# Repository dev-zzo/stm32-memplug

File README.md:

# stm32-memplug

The `stm32-memplug` project aims to be a universal toy for playing with
various memory ICs. As is obvious from the name, it is based on the STM32
SoC series, more specifically the ever-popular STM32F103 chips.

The firmware bit sits on top of the code kindly provided by the
manufacturer, the "STM32CubeF1 MCU Firmware Package". At least some part
of it will have to be rewritten later to support the flexibility I want it
to have.

The hardware bit mostly relies on the FSMC unit to handle all the signalling
for NOR, NAND, and eMMC chips.

**CAUTION**: The hardware supports 3v3 chips only. 1v8 chips **will** be destroyed.

# Why would you even?

> Science is not about *why*! It's about *why not*?

This toy is meant for learning and experimenting, not for any kind of
"professional work". Hack it and have fun while learning about the F103
and different memory types.

# How to do anything useful with this?

The toy relies on PA3..0 to detect which memory type it should configure:

PA3..0 | Memory type
-------|------------
0000 | eMMC
0001 | NAND
0011 | NOR
Other | Reserved

If you forget to set those pins to known values, the board will show up as
`STM32-MemPlug: Unknown TOP` in your USB devices.

## eMMC devices

Connect your eMMC chip to the STM32F103 board:

eMMC pin | F103 pin
---------|---------
CLK | PC12
CMD | PD2
D0 | PC8
D1 | PC9
D2 | PC10
D3 | PC11
nRST | PA8

eMMC D4 through D7 are not used anyway at this point (see Performance).
Remember to connect 3.3V and GND too! Note that some eMMC chips will require
connecting most or all power pads.

Both standard and high capacity devices should be supported.

If everything works fine, the device will appear as a simple USB mass storage
when connected to the host system. When the chip is accessed, the PC13 LED
will light up for visual confirmation.

### Wishlist

* Accessing boot partitions

## NOR devices

The current firmware supports x16 parallel-NOR chips. Wire them up like this:

NOR pin | F103 pin
--------|---------
 A0 | PF0
 A1 | PF1
 A2 | PF2
 A3 | PF3
 A4 | PF4
 A5 | PF5
 A6 | PF12
 A7 | PF13
 A8 | PF14
 A9 | PF15
A10 | PG0
A11 | PG1
A12 | PG2
A13 | PG3
A14 | PG4
A15 | PG5
A16 | PD11
A17 | PD12
A18 | PD13
A19 | PE3
A20 | PE4
A21 | PE5
A22 | PE6
A23 | PE2
A24 | PG13
A15 | PG14
 D0 | PD14
 D1 | PD15
 D2 | PD0
 D3 | PD1
 D4 | PE7
 D5 | PE8
 D6 | PE9
 D7 | PE10
 D8 | PE11
 D9 | PE12
D10 | PE13
D11 | PE14
D12 | PE15
D13 | PD8
D14 | PD9
D15 | PD10
nCE | PD7
nOE | PD4
nWE | PD5
R/B | PD6

Note the `R/B` signal might need a 10k pull-up; the internal pull-up might be
too weak to be fast enough.

## NAND devices

That is yet to come. :-)

# Building firmware

A Makefile is provided which should do that for you. Just run `make` from the
root dir. The script relies on the `CROSS_COMPILE` environment variable to
find the right compiler; it should be set to the path and prefix of your ARM
compiler; for example, it's `~/x-tools/arm-none-eabi/bin/arm-none-eabi-` on my system.

# Building hardware

If you don't want to wire small things all the time, several board designs have been
created as a semi-permanent solution. You can find those designs under `hardware`.

The general approach is, one "top" board is provided for each memory type, this goes
directly on top of the STM32F103ZE "minimal system board" (the cheapest option).
The top board provides wiring and passives as needed and accepts a set of small
footprint-specific boards; you can solder your target to those boards for reliable
and fast connection.

This is especially useful for BGA chips:

* Removing them from the device-under-hack requires hot air / rework station anyway
* Reballing the chip needs to be done anyway, doing it twice doesn't take as long

# Performance

The design is limited mostly by the USB unit of the F103 at the moment.
The theoretical speed is no greater than 1MB/s, so don't expect blazing
rates here. Transfer speeds are about 250KB/s writing and 450KB/s reading.

NOR Flash read speeds tend to land somewhere around 700KB/s.

# Debugging

The toy uses Serial Wire Output (SWO) to pring debugging messages in cases when
things go sideways; having a dongle which is able to receive that is advised.

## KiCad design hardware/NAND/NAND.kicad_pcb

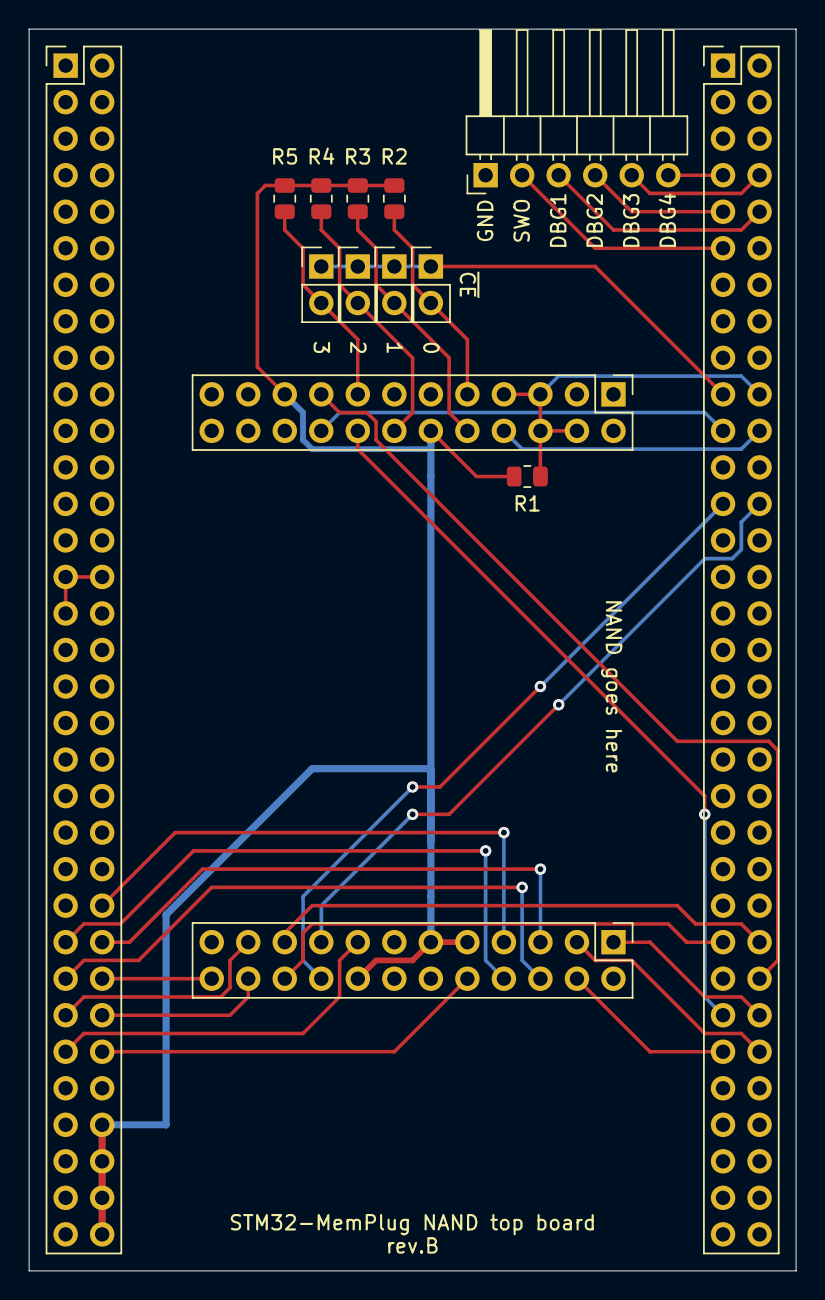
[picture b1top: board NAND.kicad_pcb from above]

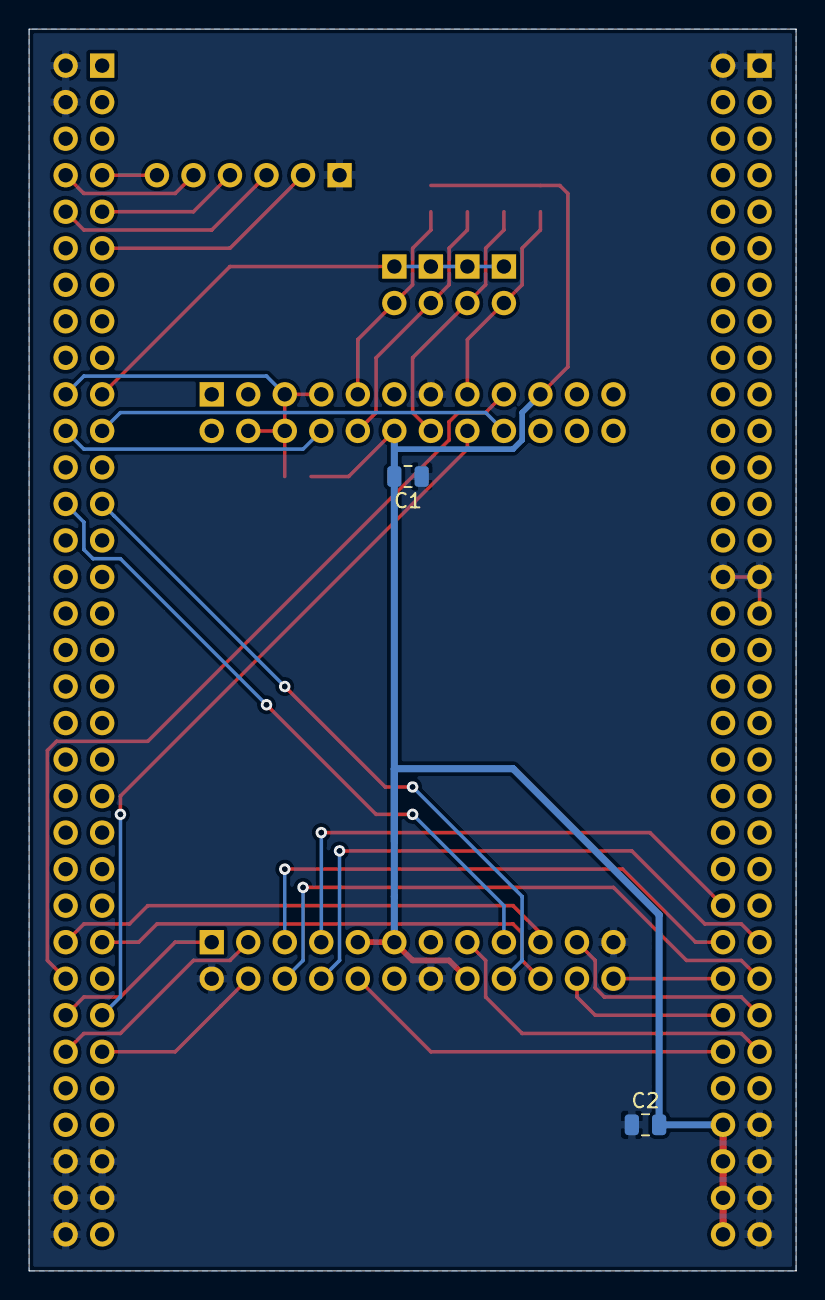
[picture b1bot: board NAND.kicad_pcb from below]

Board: 2 copper layers, 53.3 x 86.4 mm, 16 parts (2 on the bottom side), 33 nets.

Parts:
C1, C2: 100n; C_0805_2012Metric
J1: Left; PinHeader_2x33_P2.54mm_Vertical
J2: Right; PinHeader_2x33_P2.54mm_Vertical
J3: DBG; PinHeader_1x06_P2.54mm_Horizontal
J4: Left; PinHeader_2x12_P2.54mm_Vertical
J5: Right; PinHeader_2x12_P2.54mm_Vertical
JP1: CE0; PinHeader_1x02_P2.54mm_Vertical
JP2: CE1; PinHeader_1x02_P2.54mm_Vertical
JP3: CE2; PinHeader_1x02_P2.54mm_Vertical
JP4: CE3; PinHeader_1x02_P2.54mm_Vertical
R1: 1k; R_0805_2012Metric
R2, R3, R4, R5: 10k; R_0805_2012Metric

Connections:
+3V3: C1.2, C2.2, J1.60, J1.62, J1.64, J1.66, J4.12, J4.19, J5.9, J5.11, J5.16, R1.1, R2.1, R3.1, R4.1, R5.1
ALE: J2.52, J4.17
CLE: J2.53, J4.16
GND: C1.1, C2.1, J1.1, J1.2, J1.29, J1.30, J1.59, J1.61, J1.63, J1.65, J2.2, J2.4, J2.61, J2.62, J2.63, J2.64, J2.66, J3.1, J4.13, J5.2, J5.14, J5.23
IO0: J2.50, J5.19
IO1: J2.49, J5.20
IO2: J2.26, J5.17
IO3: J2.25, J5.18
IO4: J1.48, J5.7
IO5: J1.49, J5.8
IO6: J1.50, J5.5
IO7: J1.51, J5.6
IO8: J1.52, J5.24
IO9: J1.53, J5.21
IO10: J1.54, J5.22
IO11: J1.55, J5.15
IO12: J1.56, J5.10
IO13: J2.56, J5.3
IO14: J2.55, J5.4
IO15: J2.54, J5.1
PB3: J2.11, J3.2
PB4: J2.10, J3.3
PB5: J2.9, J3.4
PB6: J2.8, J3.5
PB7: J2.7, J3.6
R~B: J2.20, J4.4, J4.5, J4.6, J4.7, R1.2
~CE: J2.19, JP1.1, JP2.1, JP3.1, JP4.1
~CE0: J4.9, JP1.2, R2.2
~CE1: J4.10, JP2.2, R3.2
~CE2: J4.14, JP3.2, R4.2
~CE3: J4.15, JP4.2, R5.2
~RE: J2.22, J4.8
~WE: J2.21, J4.18

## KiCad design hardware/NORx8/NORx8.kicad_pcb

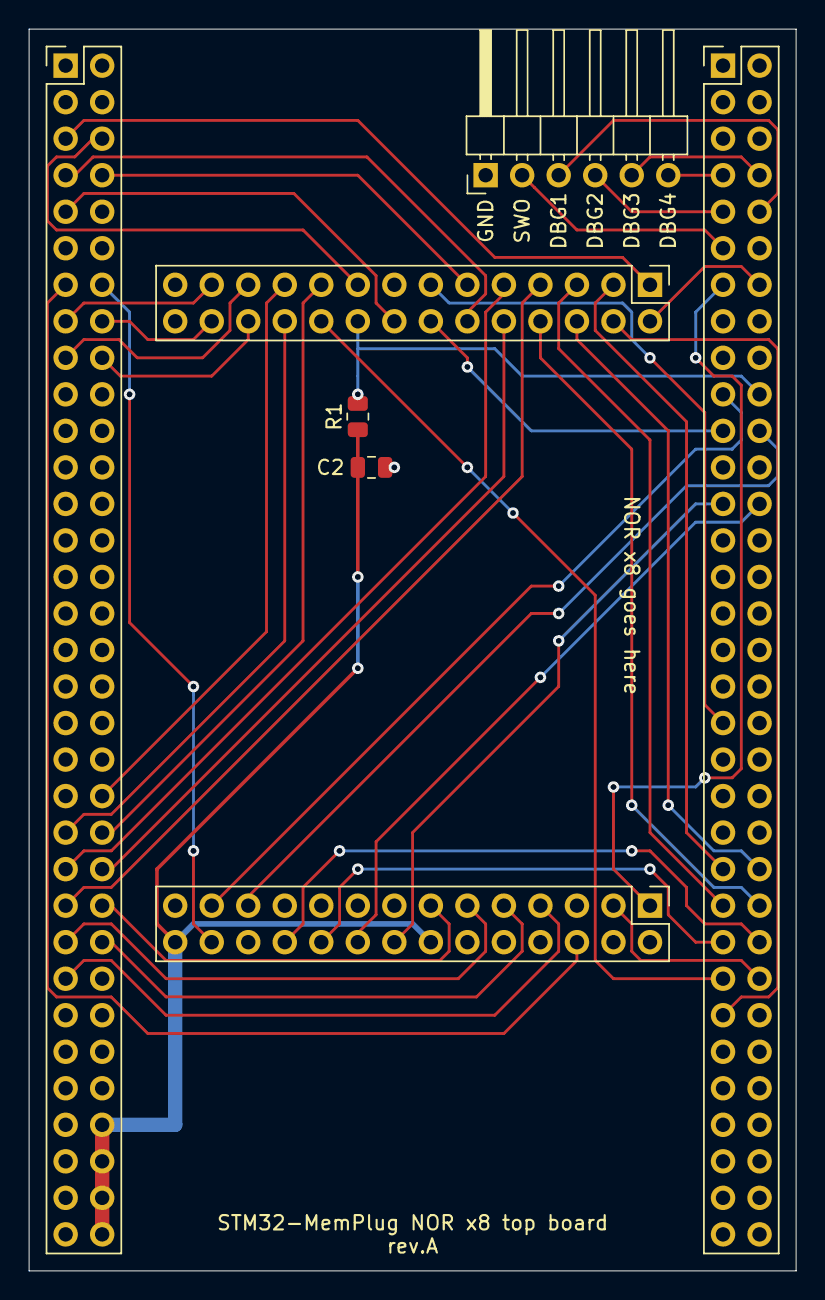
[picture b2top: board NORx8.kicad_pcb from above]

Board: 2 copper layers, 53.3 x 86.4 mm, 8 parts (1 on the bottom side), 46 nets.

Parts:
C1, C2: 100n; C_0805_2012Metric
J1: Left; PinHeader_2x33_P2.54mm_Vertical
J2: Right; PinHeader_2x33_P2.54mm_Vertical
J3: DBG; PinHeader_1x06_P2.54mm_Horizontal
J4: Left; PinHeader_2x14_P2.54mm_Vertical
J5: Right; PinHeader_2x14_P2.54mm_Vertical
R1: 10k; R_0805_2012Metric

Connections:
+3V3: C1.2, C2.2, J1.60, J1.62, J1.64, J1.66, J5.14, J5.28, R1.1
A0: J1.13, J5.6
A1: J1.14, J5.26
A2: J1.15, J4.25
A3: J1.16, J4.26
A4: J1.17, J4.23
A5: J1.18, J4.24
A6: J1.42, J4.21
A7: J1.43, J4.22
A8: J1.44, J4.19
A9: J1.45, J4.9
A10: J1.46, J4.10
A11: J1.47, J4.7
A12: J2.48, J4.8
A13: J2.47, J4.5
A14: J2.46, J4.6
A15: J2.45, J4.3
A16: J2.53, J4.4
A17: J2.52, J5.3
A18: J2.51, J4.20
A19: J1.6, J4.17
A20: J1.7, J4.12
A21: J1.8, J4.11
A22: J1.9, J4.16
A23: J1.5, J4.1
A24: J2.14, J4.2
A25: J2.13, J5.1
GND: C1.1, C2.1, J1.1, J1.2, J1.28, J1.30, J1.31, J1.59, J1.61, J1.63, J1.65, J2.2, J2.4, J2.61, J2.62, J2.63, J2.64, J2.66, J3.1, J5.5, J5.24
IO0: J2.50, J5.22
IO1: J2.49, J5.20
IO2: J2.26, J5.18
IO3: J2.25, J5.16
IO4: J1.48, J5.13
IO5: J1.49, J5.11
IO6: J1.50, J5.9
IO7: J1.51, J5.7
PB3: J2.11, J3.2
PB4: J2.10, J3.3
PB5: J2.9, J3.4
PB6: J2.8, J3.5
PB7: J2.7, J3.6
R~B: J2.20, J4.18, R1.2
~CE: J2.19, J5.25
~OE: J2.22, J5.23
~RST: J2.37, J4.13
~WE: J2.21, J4.14

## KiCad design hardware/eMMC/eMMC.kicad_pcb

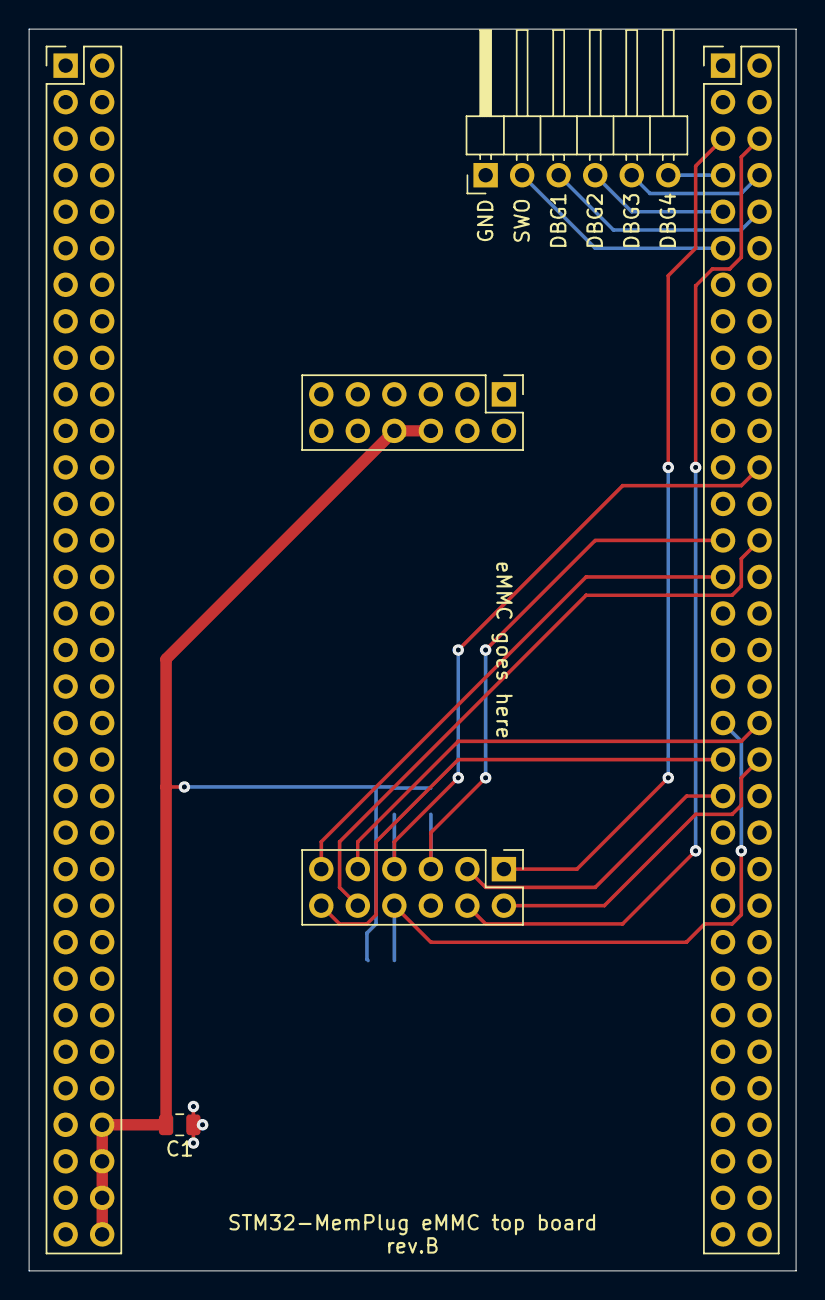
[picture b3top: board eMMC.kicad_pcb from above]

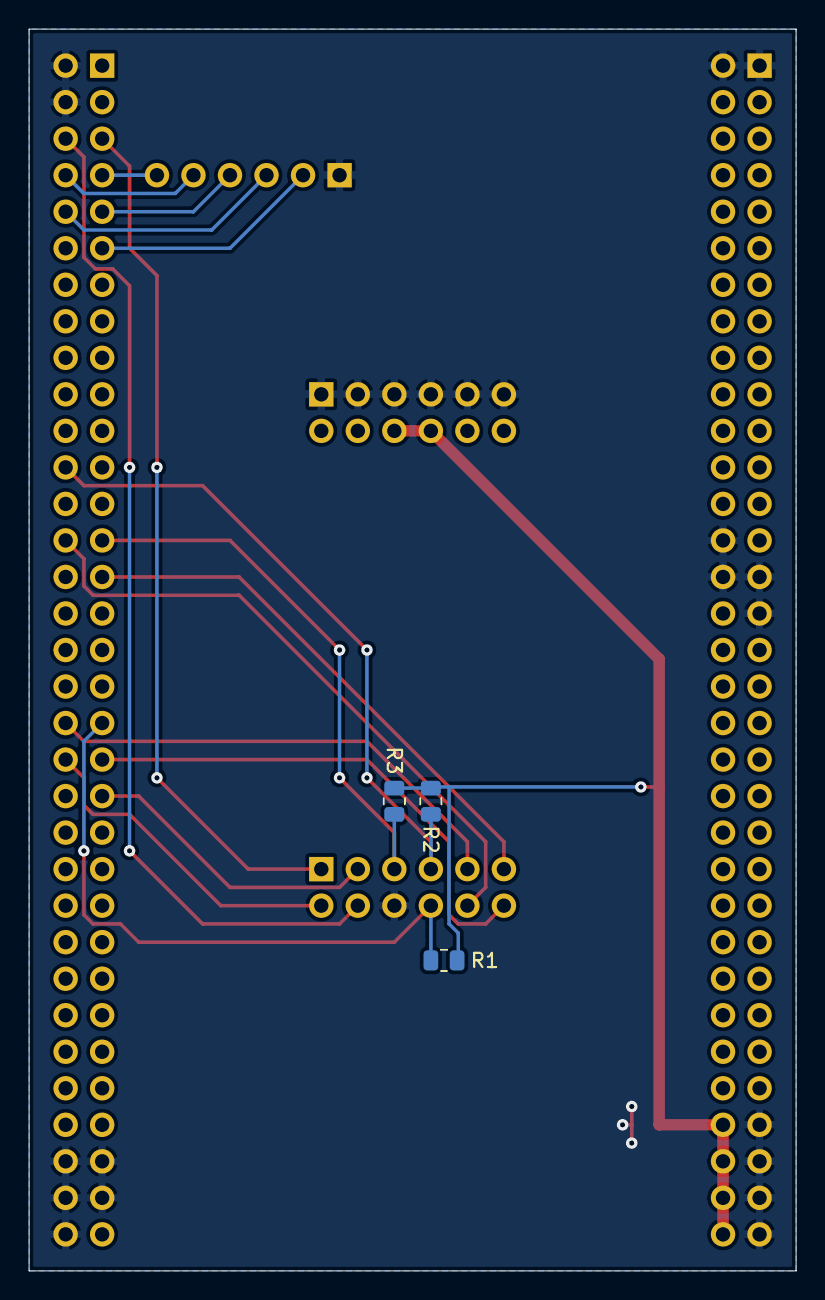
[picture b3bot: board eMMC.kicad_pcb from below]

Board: 2 copper layers, 53.3 x 86.4 mm, 9 parts (3 on the bottom side), 18 nets.

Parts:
C1: 100n; C_0805_2012Metric
J1: Left; PinHeader_2x33_P2.54mm_Vertical
J2: Right; PinHeader_2x33_P2.54mm_Vertical
J3: DBG; PinHeader_1x06_P2.54mm_Horizontal
J4: Left; PinHeader_2x06_P2.54mm_Vertical
J5: Right; PinHeader_2x06_P2.54mm_Vertical
R1, R2, R3: 10k; R_0805_2012Metric

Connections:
+3V3: C1.2, J1.60, J1.62, J1.64, J1.66, J4.6, J4.8, R1.1, R2.1, R3.1
CLK: J2.27, J5.5, R3.2
CMD: J2.24, J5.7, R2.2
DAT0: J2.39, J5.12
DAT1: J2.38, J5.9
DAT2: J2.29, J5.11
DAT3: J2.28, J5.10
DAT4: J2.6, J5.4
DAT5: J2.5, J5.1
DAT6: J2.41, J5.3
DAT7: J2.40, J5.2
GND: C1.1, J1.1, J1.2, J1.28, J1.29, J1.30, J1.31, J1.59, J1.61, J1.63, J1.65, J2.2, J2.4, J2.61, J2.62, J2.63, J2.64, J2.66, J3.1, J4.1, J4.3, J4.5, J4.7, J4.9, J4.11, J5.6
PB3: J2.11, J3.2
PB4: J2.10, J3.3
PB5: J2.9, J3.4
PB6: J2.8, J3.5
PB7: J2.7, J3.6
~RST: J2.37, J5.8, R1.2

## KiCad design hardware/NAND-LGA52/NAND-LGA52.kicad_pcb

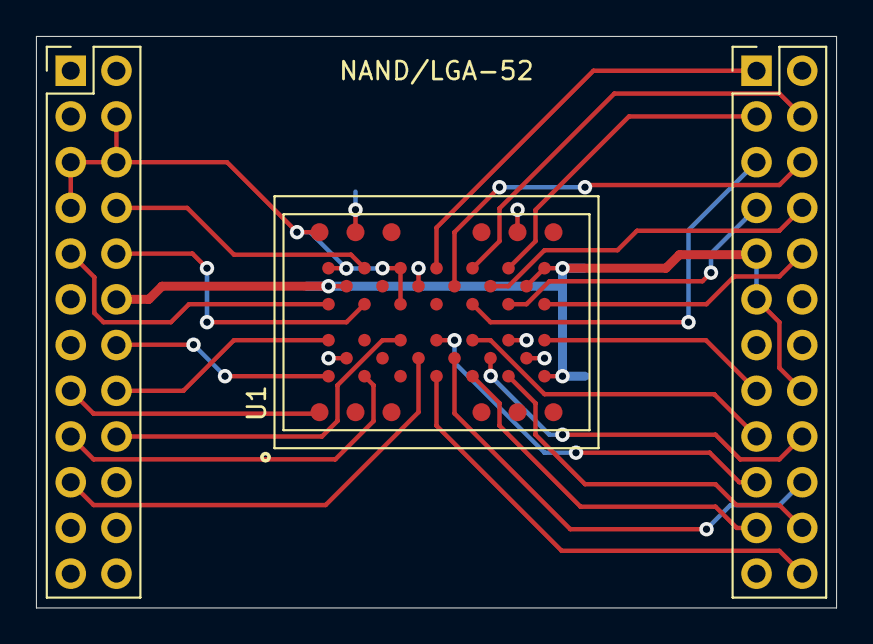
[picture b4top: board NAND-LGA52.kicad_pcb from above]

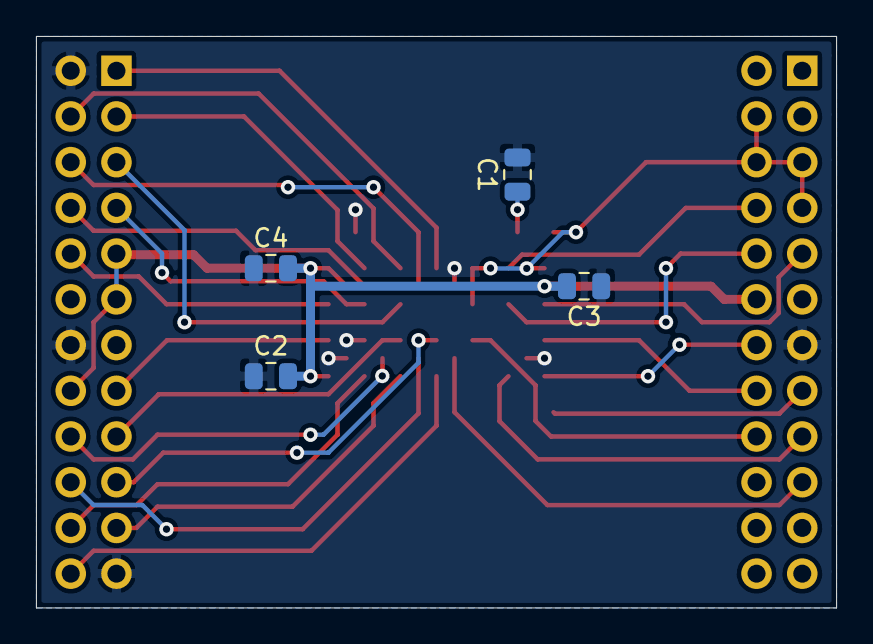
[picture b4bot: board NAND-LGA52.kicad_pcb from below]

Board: 2 copper layers, 44.4 x 31.8 mm, 7 parts (4 on the bottom side), 29 nets.

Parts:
C1, C2, C3, C4: 100n; C_0805_2012Metric
J1: Left; PinHeader_2x12_P2.54mm_Vertical
J2: Right; PinHeader_2x12_P2.54mm_Vertical
U1: Generic_ONFI_NAND_LGA52; LGA52C100P7X13_UNI

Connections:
+3V3: C2.2, C3.2, C4.2, J1.12, J2.9, J2.11, J2.16, U1.B6, U1.M6, U1.N1, U1.N7
ALE: J1.17, U1.C1
CLE: J1.16, U1.A3
GND: C1.2, C2.1, C3.1, C4.1, J1.13, J2.2, J2.14, J2.23, U1.B2, U1.F6, U1.L3, U1.M2, U1.OE8
IO0: J2.19, U1.G3
IO1: J2.20, U1.H2
IO2: J2.17, U1.J3
IO3: J2.18, U1.K2
IO4: J2.7, U1.L5
IO5: J2.8, U1.K6
IO6: J2.5, U1.J5
IO7: J2.6, U1.H6
IO8: J2.24, U1.G1
IO9: J2.21, U1.J1
IO10: J2.22, U1.L1
IO11: J2.15, U1.N3
IO12: J2.10, U1.N5
IO13: J2.3, U1.L7
IO14: J2.4, U1.J7
IO15: J2.1, U1.G7
unnamed: C1.1, U1.OB8
R~B: J1.4, J1.5, J1.6, J1.7, U1.A7, U1.E5, U1.E7, U1.OA8
~CE0: J1.9, U1.A5
~CE1: J1.10, U1.C5
~CE2: J1.14, U1.A1
~CE3: J1.15, U1.OA0
~RE: J1.8, U1.C7
~WE: J1.18, U1.E3
~WP: J1.19, U1.F2

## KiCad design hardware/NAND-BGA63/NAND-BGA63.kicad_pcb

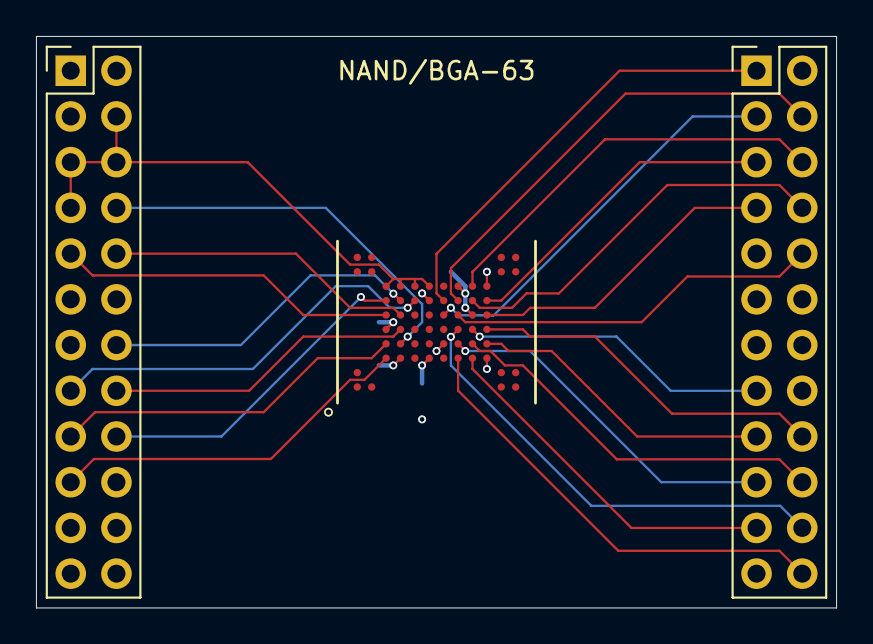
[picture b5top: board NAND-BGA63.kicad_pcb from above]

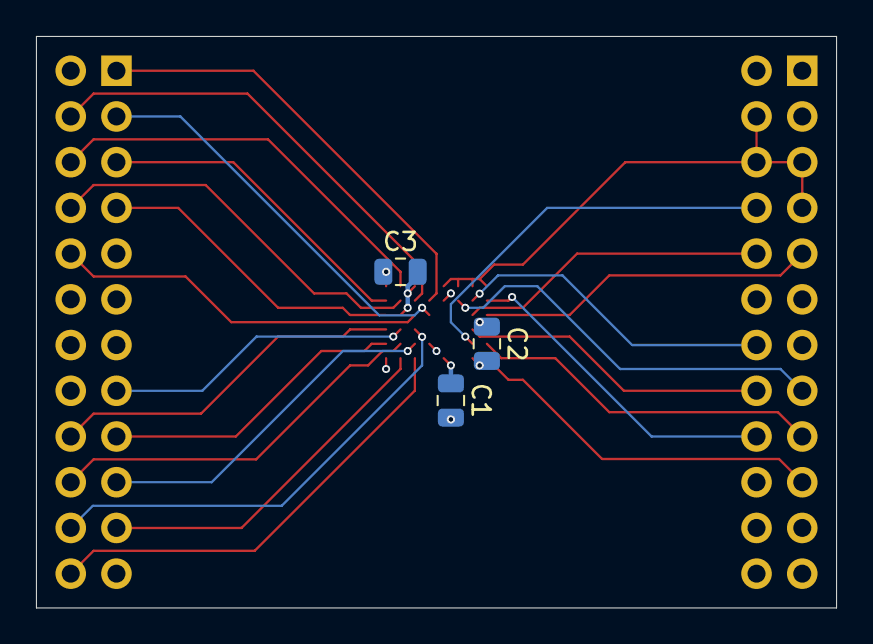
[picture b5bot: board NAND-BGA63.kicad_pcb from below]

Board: 4 copper layers, 44.5 x 31.8 mm, 6 parts (3 on the bottom side), 29 nets.

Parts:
C1, C2, C3: 100n; C_0805_2012Metric
J1: Left; PinHeader_2x12_P2.54mm_Vertical
J2: Right; PinHeader_2x12_P2.54mm_Vertical
U1: Generic_ONFI_NAND_BGA63; BGA63C80P12X10_1100X900X120

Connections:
+3V3: C2.2, C3.2, J1.12, J2.9, J2.11, J2.16, U1.D3, U1.G4, U1.H8, U1.J6
ALE: J1.17, U1.C4
CLE: J1.16, U1.D5
GND: C1.2, C2.1, C3.1, J1.13, J2.2, J2.14, J2.23, U1.C5, U1.F7, U1.K3, U1.K8
IO0: J2.19, U1.H4
IO1: J2.20, U1.J4
IO2: J2.17, U1.K4
IO3: J2.18, U1.K5
IO4: J2.7, U1.K6
IO5: J2.8, U1.J7
IO6: J2.5, U1.K7
IO7: J2.6, U1.J8
IO8: J2.24, U1.H3
IO9: J2.21, U1.J3
IO10: J2.22, U1.H5
IO11: J2.15, U1.J5
IO12: J2.10, U1.H6
IO13: J2.3, U1.G6
IO14: J2.4, U1.H7
IO15: J2.1, U1.G7
unnamed: C1.1, U1.F3
R~B: J1.4, J1.5, J1.6, J1.7, U1.C8, U1.D8, U1.E8, U1.F8
~CE0: J1.9, U1.C6
~CE1: J1.10, U1.D6
~CE2: J1.14, U1.D7
~CE3: J1.15, U1.E7
~RE: J1.8, U1.D4
~WE: J1.18, U1.C7
~WP: J1.19, U1.C3

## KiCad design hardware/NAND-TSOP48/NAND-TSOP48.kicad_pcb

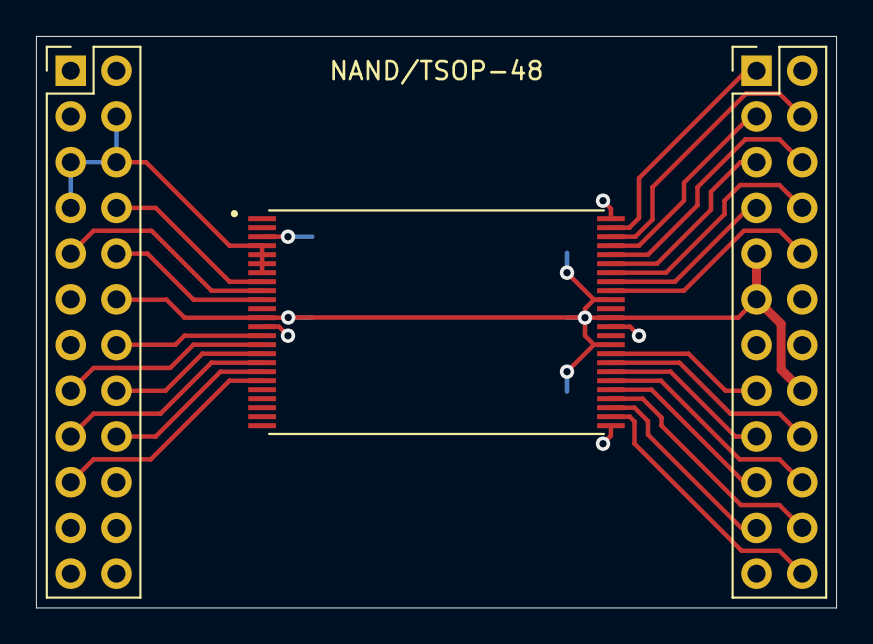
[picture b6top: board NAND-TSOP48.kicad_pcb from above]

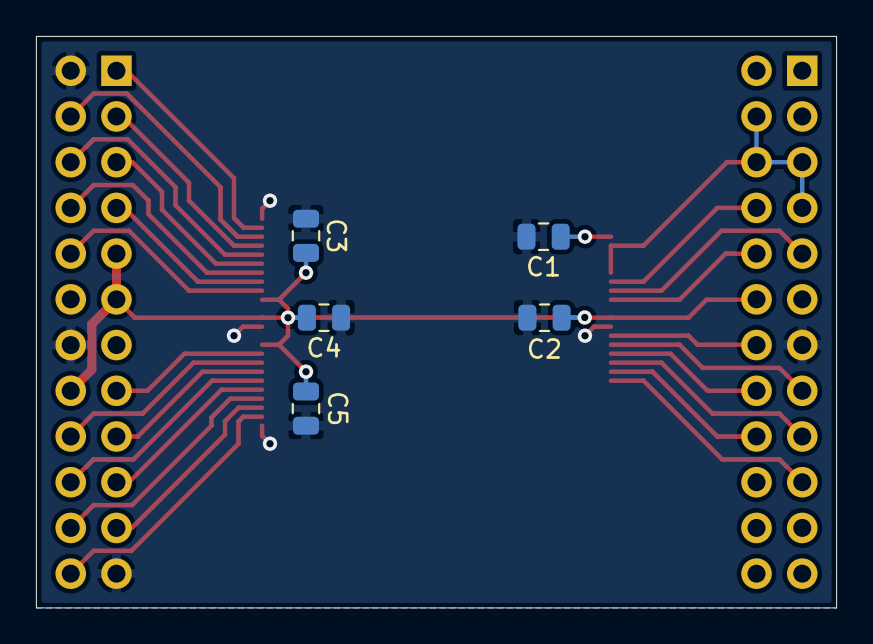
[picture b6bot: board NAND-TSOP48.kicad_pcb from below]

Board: 2 copper layers, 44.5 x 31.7 mm, 8 parts (5 on the bottom side), 29 nets.

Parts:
C1, C2, C3, C4, C5: 100n; C_0805_2012Metric
J1: Left; PinHeader_2x12_P2.54mm_Vertical
J2: Right; PinHeader_2x12_P2.54mm_Vertical
U1: Generic_ONFI_NAND_TSOP48; SOP50P2000X120-48N

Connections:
+3V3: C2.2, C3.2, C4.2, C5.2, J1.12, J2.9, J2.11, J2.16, U1.12, U1.34, U1.37, U1.39
ALE: J1.17, U1.17
CLE: J1.16, U1.16
GND: C1.2, C2.1, C3.1, C4.1, C5.1, J1.13, J2.2, J2.14, J2.23, U1.13, U1.25, U1.36, U1.48
IO0: J2.19, U1.29
IO1: J2.20, U1.30
IO2: J2.17, U1.31
IO3: J2.18, U1.32
IO4: J2.7, U1.41
IO5: J2.8, U1.42
IO6: J2.5, U1.43
IO7: J2.6, U1.44
IO8: J2.24, U1.26
IO9: J2.21, U1.27
IO10: J2.22, U1.28
IO11: J2.15, U1.33
IO12: J2.10, U1.40
IO13: J2.3, U1.45
IO14: J2.4, U1.46
IO15: J2.1, U1.47
unnamed: C1.1, U1.3
R~B: J1.4, J1.5, J1.6, J1.7, U1.4, U1.5, U1.6, U1.7
~CE0: J1.9, U1.9
~CE1: J1.10, U1.10
~CE2: J1.14, U1.14
~CE3: J1.15, U1.15
~RE: J1.8, U1.8
~WE: J1.18, U1.18
~WP: J1.19, U1.19

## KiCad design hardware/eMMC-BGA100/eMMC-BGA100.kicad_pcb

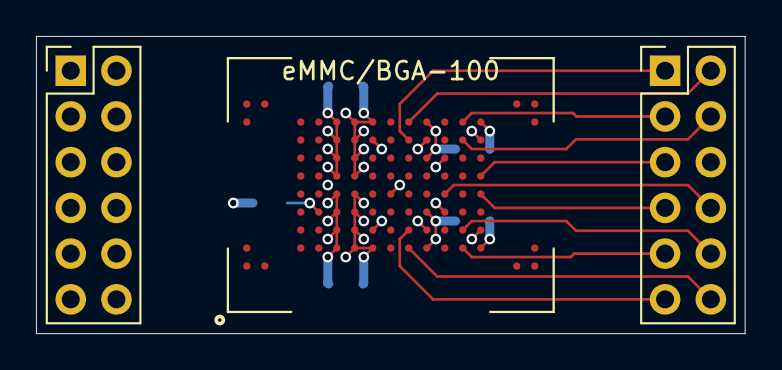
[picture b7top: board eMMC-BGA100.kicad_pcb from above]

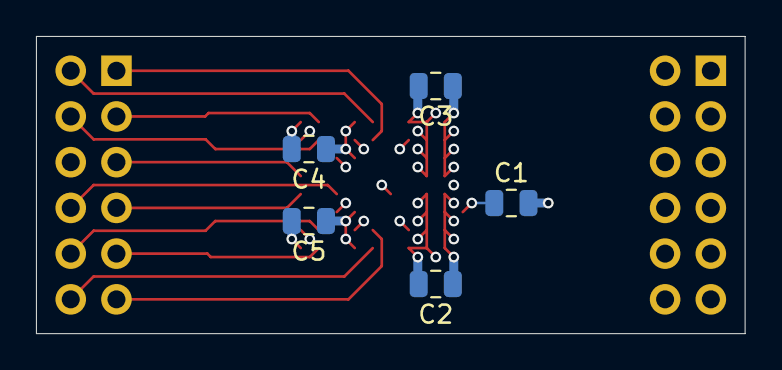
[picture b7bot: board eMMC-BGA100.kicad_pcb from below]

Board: 4 copper layers, 39.4 x 16.5 mm, 8 parts (5 on the bottom side), 14 nets.

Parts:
C1, C2, C3, C4, C5: 100n; C_0805_2012Metric
J1: Left; PinHeader_2x06_P2.54mm_Vertical
J2: Right; PinHeader_2x06_P2.54mm_Vertical
U1: Generic_eMMC_BGA100; BGA100C100P17X10_1800X1400X140N

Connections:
+3V3: C2.1, C3.1, C4.1, C5.1, J1.6, J1.8, U1.F2, U1.F3, U1.F4, U1.F5, U1.F6, U1.F7, U1.F8, U1.F9, U1.H3, U1.H8, U1.L2, U1.L4, U1.L7, U1.L9, U1.P3, U1.P8
CLK: J2.5, U1.P6
CMD: J2.7, U1.P5
DAT0: J2.12, U1.K2
DAT1: J2.9, U1.N2
DAT2: J2.11, U1.K3
DAT3: J2.10, U1.N3
DAT4: J2.4, U1.N8
DAT5: J2.1, U1.K8
DAT6: J2.3, U1.N9
DAT7: J2.2, U1.K9
GND: C1.2, C2.2, C3.2, C4.2, C5.2, J1.1, J1.3, J1.5, J1.7, J1.9, J1.11, J2.6, U1.G2, U1.G3, U1.G4, U1.G5, U1.G6, U1.G7, U1.G8, U1.G9, U1.H2, U1.H9, U1.J5, U1.L3, U1.L8, U1.M4, U1.M7, U1.P2, U1.P9
unnamed: C1.1, U1.E4
~RST: J2.8, U1.M5

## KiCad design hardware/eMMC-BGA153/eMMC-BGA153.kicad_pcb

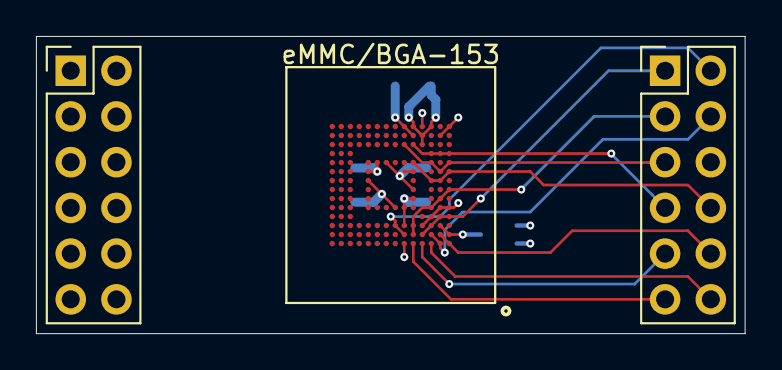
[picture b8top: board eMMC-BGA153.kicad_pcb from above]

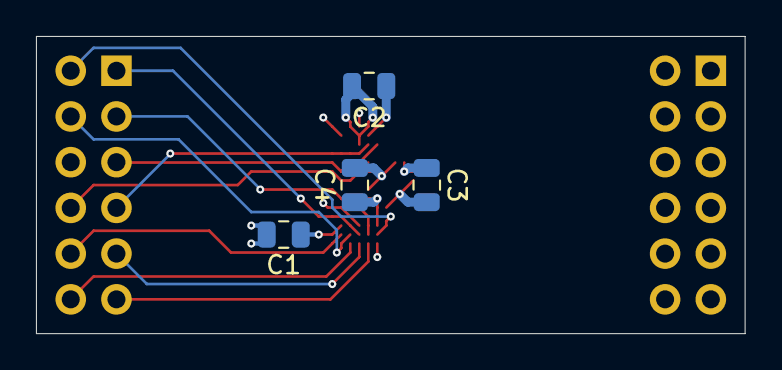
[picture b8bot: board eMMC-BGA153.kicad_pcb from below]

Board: 4 copper layers, 39.4 x 16.5 mm, 7 parts (4 on the bottom side), 14 nets.

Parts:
C1, C2, C3, C4: 100n; C_0805_2012Metric
J1: Left; PinHeader_2x06_P2.54mm_Vertical
J2: Right; PinHeader_2x06_P2.54mm_Vertical
U1: Generic_eMMC_BGA153; BGA153N50P14X14_1150X1300X100

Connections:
+3V3: C2.1, C3.1, C4.1, J1.6, J1.8, U1.C6, U1.E6, U1.F5, U1.J10, U1.K9, U1.M4, U1.N4, U1.P3, U1.P5
CLK: J2.5, U1.J2, U1.K1, U1.K3, U1.M6
CMD: J2.7, U1.L1, U1.L2, U1.L3, U1.M5
DAT0: J2.12, U1.A3
DAT1: J2.9, U1.A4
DAT2: J2.11, U1.A5
DAT3: J2.10, U1.A1, U1.B2
DAT4: J2.4, U1.A2, U1.B3
DAT5: J2.1, U1.B4, U1.C3, U1.D1, U1.D2
DAT6: J2.3, U1.B5, U1.C5, U1.E3, U1.F2, U1.G1
DAT7: J2.2, U1.B6, U1.C7
GND: C1.2, C2.2, C3.2, C4.2, J1.1, J1.3, J1.5, J1.7, J1.9, J1.11, J2.6, U1.A6, U1.C4, U1.D3, U1.E1, U1.E2, U1.E7, U1.G5, U1.H10, U1.J5, U1.K8, U1.N2, U1.N5, U1.P1, U1.P4, U1.P6
unnamed: C1.1, U1.B1, U1.C2
~RST: J2.8, U1.H2, U1.H3, U1.J1, U1.K5

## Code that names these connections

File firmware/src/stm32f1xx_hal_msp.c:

/**
  ******************************************************************************
  * @file    Templates/Src/stm32f1xx_hal_msp.c
  * @author  MCD Application Team
  * @brief   HAL MSP module.
  ******************************************************************************
  * @attention
  *
  * <h2><center>&copy; Copyright (c) 2016 STMicroelectronics.
  * All rights reserved.</center></h2>
  *
  * This software component is licensed by ST under BSD 3-Clause license,
  * the "License"; You may not use this file except in compliance with the
  * License. You may obtain a copy of the License at:
  *                        opensource.org/licenses/BSD-3-Clause
  *
  ******************************************************************************
  */

/* Includes ------------------------------------------------------------------*/
#include "stm32f1xx_hal.h"
#include "debug.h"
#include "nor_driver.h"
#include "nand_driver.h"

/** @addtogroup STM32F1xx_HAL_Examples
  * @{
  */

/** @addtogroup Templates
  * @{
  */

/* Private typedef -----------------------------------------------------------*/
/* Private define ------------------------------------------------------------*/
/* Private macro -------------------------------------------------------------*/
/* Private variables ---------------------------------------------------------*/
/* Private function prototypes -----------------------------------------------*/
/* Private functions ---------------------------------------------------------*/

/** @defgroup HAL_MSP_Private_Functions
  * @{
  */

/**
  * @brief  Initializes the Global MSP.
  * @param  None
  * @retval None
  */
void HAL_MspInit(void)
{
    GPIO_InitTypeDef gpio;

    __HAL_RCC_GPIOA_CLK_ENABLE();
    __HAL_RCC_GPIOA_RELEASE_RESET();

    /* Init the RESET output */
    gpio.Pin = GPIO_PIN_8;
    gpio.Mode = GPIO_MODE_OUTPUT_PP;
    gpio.Speed = GPIO_SPEED_FREQ_MEDIUM;
    HAL_GPIO_Init(GPIOA, &gpio);
    /* Set the RESET output to active */
    HAL_GPIO_WritePin(GPIOA, GPIO_PIN_8, GPIO_PIN_RESET);
}

void MEM_ControlRST(int state)
{
    HAL_GPIO_WritePin(GPIOA, GPIO_PIN_8, state ? GPIO_PIN_RESET : GPIO_PIN_SET);
}

/**
  * @brief  DeInitializes the Global MSP.
  * @param  None
  * @retval None
  */
void HAL_MspDeInit(void)
{
}

/**
  * @brief  Initializes the MMC MSP.
  * @param  hmmc: Pointer to MMC handle
  * @retval None
  */
void HAL_MMC_MspInit(MMC_HandleTypeDef* hmmc)
{
    GPIO_InitTypeDef gpio;

    __HAL_RCC_GPIOC_CLK_ENABLE();
    __HAL_RCC_GPIOD_CLK_ENABLE();
    __HAL_RCC_GPIOC_RELEASE_RESET();
    __HAL_RCC_GPIOD_RELEASE_RESET();
    __HAL_RCC_SDIO_CLK_ENABLE();
    __HAL_RCC_AFIO_CLK_ENABLE();

    gpio.Mode = GPIO_MODE_AF_PP;
    gpio.Pull = GPIO_PULLUP;
    gpio.Speed = GPIO_SPEED_FREQ_HIGH;

    gpio.Pin =
         GPIO_PIN_12    /* CLK */
        |GPIO_PIN_11    /* D3 */
        |GPIO_PIN_10    /* D2 */
        |GPIO_PIN_9     /* D1 */
        |GPIO_PIN_8     /* D0 */
        ;
    HAL_GPIO_Init(GPIOC, &gpio);

    gpio.Pin = GPIO_PIN_2;  /* CMD */
    HAL_GPIO_Init(GPIOD, &gpio);
}

/**
  * @brief  Initializes the FSMC NOR MSP.
  * @param  hnor: Pointer to NOR handle
  * @retval None
  */
void NOR_MspInit(NOR_Handle_t *hnor)
{
	GPIO_InitTypeDef gpio;

    __HAL_RCC_AFIO_CLK_ENABLE();
    __HAL_RCC_FSMC_CLK_ENABLE();

    gpio.Pull = GPIO_PULLUP;
    gpio.Speed = GPIO_SPEED_FREQ_HIGH;
    gpio.Mode = GPIO_MODE_AF_PP;

    __HAL_RCC_GPIOD_CLK_ENABLE();
    __HAL_RCC_GPIOD_RELEASE_RESET();
    gpio.Pin =
         GPIO_PIN_0     /* D2 */
        |GPIO_PIN_1     /* D3 */
        |GPIO_PIN_4     /* nRE */
        |GPIO_PIN_5     /* nWE */
        |GPIO_PIN_7     /* CE */
        |GPIO_PIN_8     /* D13 */
        |GPIO_PIN_9     /* D14 */
        |GPIO_PIN_10    /* D15 or A-1 */
        |GPIO_PIN_11    /* A16 */
        |GPIO_PIN_12    /* A17 */
        |GPIO_PIN_13    /* A18 */
        |GPIO_PIN_14    /* D0 */
        |GPIO_PIN_15    /* D1 */
        ;
    HAL_GPIO_Init(GPIOD, &gpio);

    __HAL_RCC_GPIOE_CLK_ENABLE();
    __HAL_RCC_GPIOE_RELEASE_RESET();
    gpio.Pin =
         GPIO_PIN_2     /* A23 */
        |GPIO_PIN_3     /* A19 */
        |GPIO_PIN_4     /* A20 */
        |GPIO_PIN_5     /* A21 */
        |GPIO_PIN_6     /* A22 */
        |GPIO_PIN_7     /* D4 */
        |GPIO_PIN_8     /* D5 */
        |GPIO_PIN_9     /* D6 */
        |GPIO_PIN_10    /* D7 */
        |GPIO_PIN_11    /* D8 */
        |GPIO_PIN_12    /* D9 */
        |GPIO_PIN_13    /* D10 */
        |GPIO_PIN_14    /* D11 */
        |GPIO_PIN_15    /* D12 */
        ;
    HAL_GPIO_Init(GPIOE, &gpio);

    __HAL_RCC_GPIOF_CLK_ENABLE();
    __HAL_RCC_GPIOF_RELEASE_RESET();
    gpio.Pin =
         GPIO_PIN_0     /* A0 */
        |GPIO_PIN_1     /* A1 */
        |GPIO_PIN_2     /* A2 */
        |GPIO_PIN_3     /* A3 */
        |GPIO_PIN_4     /* A4 */
        |GPIO_PIN_5     /* A5 */
        |GPIO_PIN_12    /* A6 */
        |GPIO_PIN_13    /* A7 */
        |GPIO_PIN_14    /* A8 */
        |GPIO_PIN_15    /* A9 */
        ;
    HAL_GPIO_Init(GPIOF, &gpio);

    __HAL_RCC_GPIOG_CLK_ENABLE();
    __HAL_RCC_GPIOG_RELEASE_RESET();
    gpio.Pin =
         GPIO_PIN_0     /* A10 */
        |GPIO_PIN_1     /* A11 */
        |GPIO_PIN_2     /* A12 */
        |GPIO_PIN_3     /* A13 */
        |GPIO_PIN_4     /* A14 */
        |GPIO_PIN_5     /* A15 */
        |GPIO_PIN_13    /* A24 */
        |GPIO_PIN_14    /* A25 */
        ;
    HAL_GPIO_Init(GPIOG, &gpio);

    gpio.Pin = GPIO_PIN_6;  /* R/B */
    gpio.Mode = GPIO_MODE_INPUT;
    gpio.Pull = GPIO_PULLUP;
    HAL_GPIO_Init(GPIOD, &gpio);
}

/**
  * @brief  Initializes the FSMC NAND MSP.
  * @param  hnand: Pointer to NAND handle
  * @retval None
  */
void NAND_MspInit(NAND_Handle_t *hnand)
{
	GPIO_InitTypeDef gpio = {0};

    __HAL_RCC_AFIO_CLK_ENABLE();
    __HAL_RCC_FSMC_CLK_ENABLE();

    gpio.Pull = GPIO_PULLUP;
    gpio.Speed = GPIO_SPEED_FREQ_HIGH;
    gpio.Mode = GPIO_MODE_AF_PP;

    __HAL_RCC_GPIOD_CLK_ENABLE();
    __HAL_RCC_GPIOD_RELEASE_RESET();
    gpio.Pin =
         GPIO_PIN_0     /* IO2 */
        |GPIO_PIN_1     /* IO3 */
        |GPIO_PIN_4     /* nRE */
        |GPIO_PIN_5     /* nWE */
        |GPIO_PIN_7     /* CE2 */
        |GPIO_PIN_8     /* IO13 */
        |GPIO_PIN_9     /* IO14 */
        |GPIO_PIN_10    /* IO15 */
        |GPIO_PIN_11    /* CLE */
        |GPIO_PIN_12    /* ALE */
        |GPIO_PIN_14    /* IO0 */
        |GPIO_PIN_15    /* IO1 */
        ;
    HAL_GPIO_Init(GPIOD, &gpio);

    __HAL_RCC_GPIOE_CLK_ENABLE();
    __HAL_RCC_GPIOE_RELEASE_RESET();
    gpio.Pin =
         GPIO_PIN_7     /* IO4 */
        |GPIO_PIN_8     /* IO5 */
        |GPIO_PIN_9     /* IO6 */
        |GPIO_PIN_10    /* IO7 */
        |GPIO_PIN_11    /* IO8 */
        |GPIO_PIN_12    /* IO9 */
        |GPIO_PIN_13    /* IO10 */
        |GPIO_PIN_14    /* IO11 */
        |GPIO_PIN_15    /* IO12 */
        ;
    HAL_GPIO_Init(GPIOE, &gpio);

    __HAL_RCC_GPIOG_CLK_ENABLE();
    __HAL_RCC_GPIOG_RELEASE_RESET();
    gpio.Pin = GPIO_PIN_9;  /* CE3 */
    HAL_GPIO_Init(GPIOG, &gpio);

    gpio.Mode = GPIO_MODE_INPUT;
    gpio.Pin = GPIO_PIN_6;  /* R/B */
    HAL_GPIO_Init(GPIOD, &gpio);
}

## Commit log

2021-02-21 importing all the existing stuff
2021-02-21 update the readme -- SD cards are not supported
2021-02-21 move debug output to SWO together with small code rearrangement
2021-08-15 Implement basic NOR memory interface
2021-08-16 Abandon the NOR driver from HAL
2021-08-17 Update USB middleware; commands now fail properly
2021-08-17 Add basic fault handling for debugging purposes
2021-08-17 Set the status properly on programming end
2021-08-17 Update gitignore with kicad stuff
2021-08-17 Add parallel-NOR hardware
2021-08-17 Update readme to track the progress
2021-08-17 Adding the software bits
2021-08-17 Formatting fix in README
2021-08-17 Clean up .gitignore a bit
2021-08-17 Make eMMC behave
2021-08-17 eMMC: patch ops so we wait until the end proper
2021-08-17 eMMC: add hardware
2021-08-19 Update gitignore yet again
2021-08-19 NAND: board designs rev.A added
2021-08-19 NOR: rename top board to indicate x16 only
2021-08-20 hardware: NOR x16 top to rev.B
    + Added pull-up for ready/busy
    + Modified J3 DBG to break out SWO and GPIO pins
2021-08-20 USB: fix const warning
2021-08-20 NAND: something is working now, only reading though
2021-08-20 hardware: NOR x8 top board added
2021-08-20 hardware: fix KiCAD library paths
2021-08-20 NOR: provisional support for x8 bus
2021-08-20 hardware: NAND top to rev.B
    + Modified J3 DBG to break out SWO and GPIO pins
    + FSMC CE2 can be switched to any of NAND CEx
    + Added pull-ups for NAND CEx
2021-08-20 hardware: eMMC top to rev.B
    + Harmonized daughter board orientation
    + Modified J3 DBG to break out SWO and GPIO pins
2021-08-20 hardware: update top board labels
2021-09-28 refreshed carrier boards and added missing symbol libs
2022-10-21 software update!
